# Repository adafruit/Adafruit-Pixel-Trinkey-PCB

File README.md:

## Adafruit Pixel Trinkey - USB Key for NeoPixel / DotStar Driving PCB

<a href="http://www.adafruit.com/products/5953"><br/>
Click here to purchase one from the Adafruit shop</a>

PCB files for the Adafruit Pixel Trinkey - USB Key for NeoPixel / DotStar Driving. 

Format is EagleCAD schematic and board layout
* https://www.adafruit.com/product/5953

### Description

Blast-off to Pixel Planet with the Adafruit Pixel Trinkey, a co-pilot for those who like to shine bright. This little microcontroller board plugs into your computer's USB port and can drive tons of NeoPixel (SK6812, WS2812, etc) or DotStar (e.g. AP102) LEDs without having to do any soldering or complex wiring. The SAMD21 chip on board has 32KB of SRAM, that means thousands of pixels! All from the convenience of your computer with support for Arduino, CircuitPython or Windows 11's built-in Dynamic Light Control

NeoPixels and Dotstars are 'smart' LEDs that can display 24-bit color, they're bright, colorful, individually-addressable, and come in dozens of different shapes: from flexible strips, to individual dots, to rings, and beyond. However, you need a microcontroller to drive them: something that can generate the exact pattern of data that they desire to set each pixel color. Normally folks use something like an Arduino, which will work just fine, but sometimes needs level shifting or separate power, or just has gangly wires.

This board contains the microcontroller, plus level shifting in a compact package that pokes out an inch from your computer USB port. On the end is a screw terminal block that can accept stranded or solid-core wires 26 to 18 AWG with four ports: 5V power, Data, Clock and Ground. If you're using DotStars, wire up the 'input' side of your LEDs to the 4 pads. If you're using NeoPixels, you can have one or two strands, where the second strand uses the Clock pin as the data generator.

Computer USB ports can provide up to 1A which we've found will drive about 150 pixels without difficulty as long as they are not all on full white at max brightness. If you need to drive a ton more pixels, simply disconnect the 5V power wire and use an external power source - just make sure that the ground wire from the external power is connected to the ground of the Trinkey+pixels. You can monitor the USB 5V line voltage thanks to a resistor divider on the board.

If you want to add additional circuitry, such as an Infrared remote input, or potentiometer, or a button, there's a JST-SH 3-pin connector on board. Use a JST SH 3-pin cable to access the 3V, ground and pin D4. There's also a separate mini NeoPixel for status feedback if desired.

Features:

* ATSAMD21E18 32-bit Cortex M0+ - 48 MHz 32-bit processor with 256KB Flash and 32 KB RAM
* Native USB supported by every OS - can be used in Arduino or CircuitPython as a USB serial console, MIDI, Keyboard/Mouse HID, and even a little disk drive for storing Python scripts
* Can be used with Arduino IDE or CircuitPython
* 0.1" / 2.54mm Terminal Blocks - Attach LEDs with no soldering! Just use a common screwdriver.
* On-board RGB NeoPixel LED
* JST SH 3-pin compatible connector - For extra hardware connectivity
* Reset switch to start your project code over or enter bootloader mode
* Open Source Hardware so you have full control over your LEDs

### License

Adafruit invests time and resources providing this open source design, please support Adafruit and open-source hardware by purchasing products from [Adafruit](https://www.adafruit.com)!

Designed by Limor Fried/Ladyada for Adafruit Industries.

Creative Commons Attribution/Share-Alike, all text above must be included in any redistribution. 
See license.txt for additional details.

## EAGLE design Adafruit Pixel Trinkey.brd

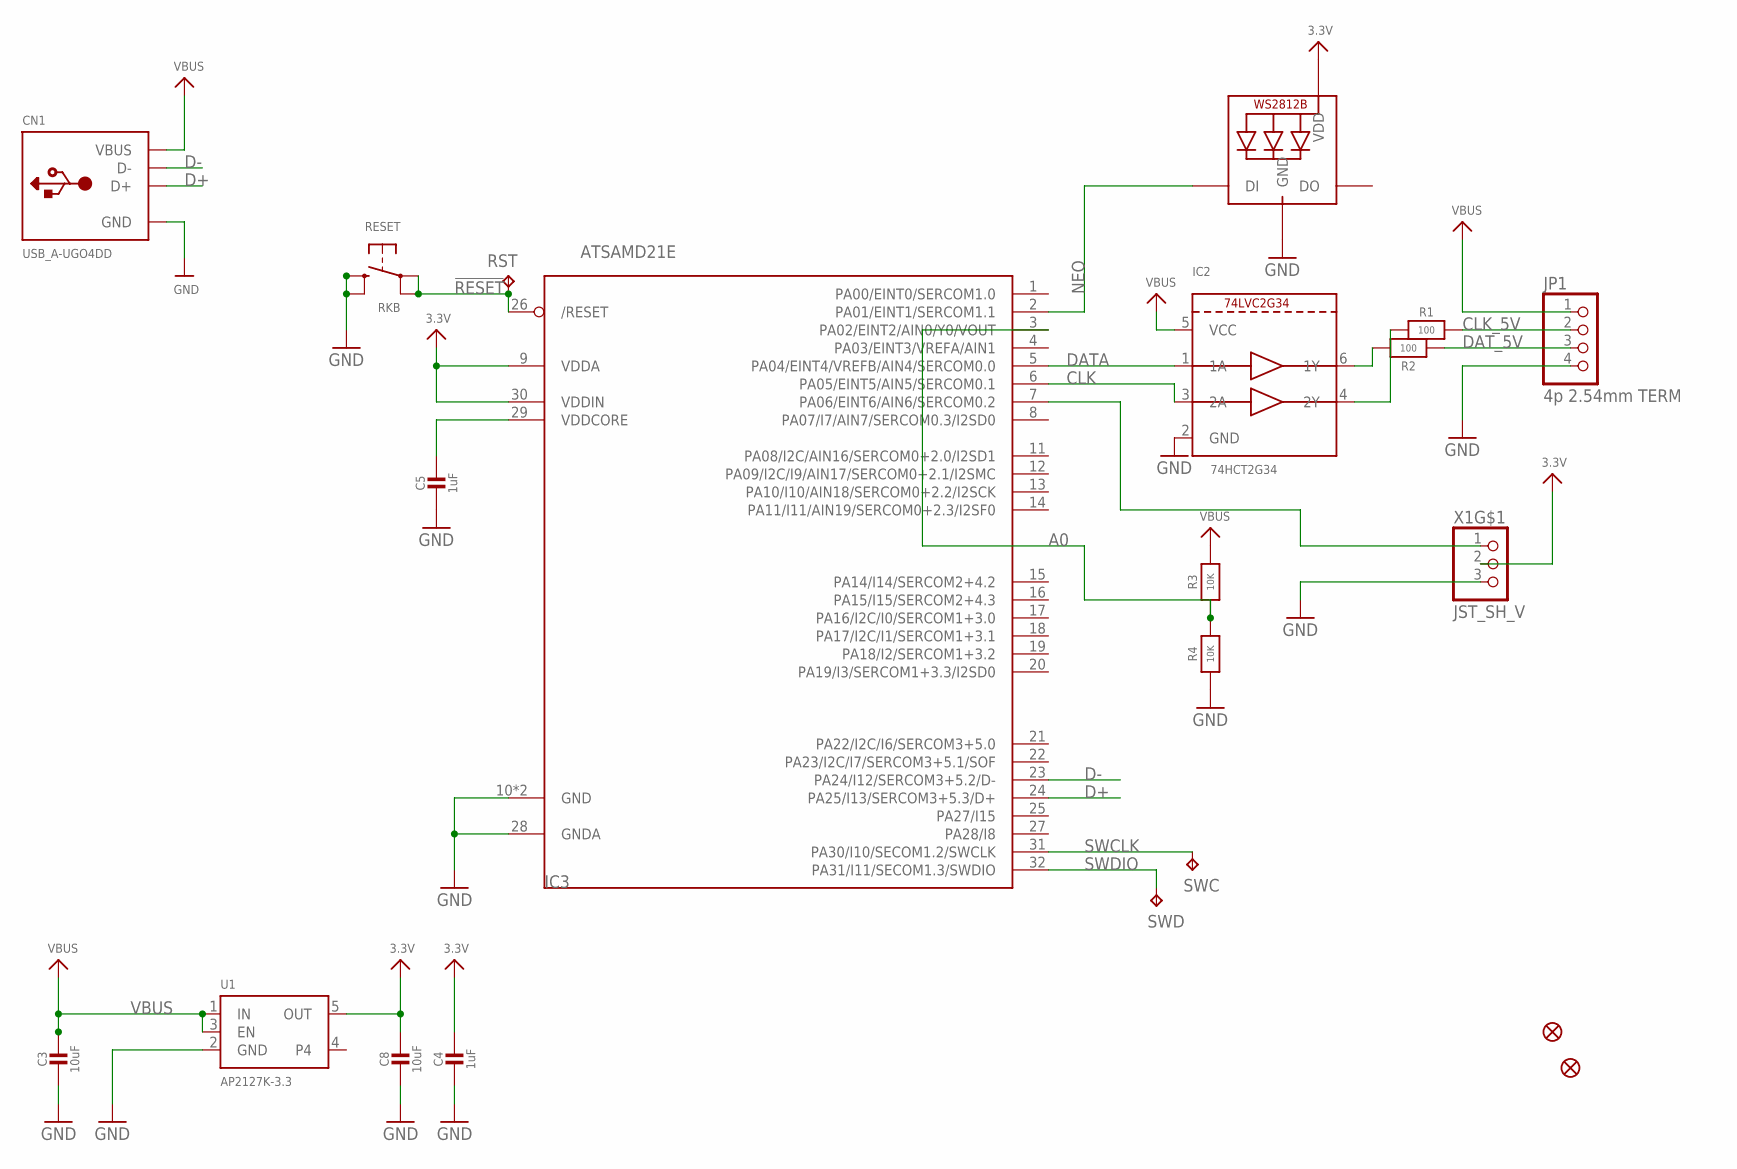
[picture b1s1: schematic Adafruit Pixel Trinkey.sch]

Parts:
C3, C8: 10uF; 0805-NO
C4, C5: 1uF; 0603-NO
CN1: USB_A-UGO4DD
FID1, FID2: FIDUCIAL_0.5MM
IC2: 74HCT2G34; SC70-6L
IC3: ATSAMD21E; QFN32_5MM
JP1: 4p 2.54mm TERM; 1X04_2.54MMTERMINAL
LED1: WS2812B_SK6805_1515; SK6805_1515
R1, R2: 100; _0402NO
R3, R4: 10K; _0402NO
RESET: RKB; BTN_RKB2_4.6X2.8
RST: TPTP16R; TP16R
SWC: TPTP15R; TP15R
SWD: TPTP16R; TP16R
U1: AP2127K-3.3; SOT23-5; JLC_ROTATION 0
X1: JST_SH_V; JST_SH3_RA

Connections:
3.3V: C4.1, C8.1, IC3.9 (VDDA), IC3.30 (VDDIN), LED1.2 (VDD), U1.5 (OUT), X1.2
!RESET: IC3.26 (/RESET), RESET.A, RESET.A' (P1), RST.TP
A0: IC3.3 (PA02/EINT2/AIN0/Y0/VOUT), R3.1, R4.2
CLK: IC2.3 (2A), IC3.6 (PA05/EINT5/AIN5/SERCOM0.1)
CLK_5V: JP1.2, R1.2
D+: CN1.D+, IC3.24 (PA25/I13/SERCOM3+5.3/D+)
D-: CN1.D-, IC3.23 (PA24/I12/SERCOM3+5.2/D-)
DATA: IC2.1 (1A), IC3.5 (PA04/EINT4/VREFB/AIN4/SERCOM0.0)
DAT_5V: JP1.3, R2.2
GND: C3.2, C4.2, C5.2, C8.2, CN1.GND, IC2.2 (GND), IC3.10 (GND), IC3.28 (GNDA), IC3.33 (GND), JP1.4, LED1.4 (GND), R4.1, RESET.B (S), RESET.B' (S1), U1.2 (GND), X1.3
unnamed: IC3.7 (PA06/EINT6/AIN6/SERCOM0.2), X1.1
unnamed: IC2.4 (2Y), R1.1
unnamed: IC2.6 (1Y), R2.1
NEO: IC3.2 (PA01/EINT1/SERCOM1.1), LED1.1 (DI)
SWCLK: IC3.31 (PA30/I10/SECOM1.2/SWCLK), SWC.TP
SWDIO: IC3.32 (PA31/I11/SECOM1.3/SWDIO), SWD.TP
VBUS: C3.1, CN1.VBUS, IC2.5 (VCC), JP1.1, R3.2, U1.1 (IN), U1.3 (EN)
VDDCORE1: C5.1, IC3.29 (VDDCORE)

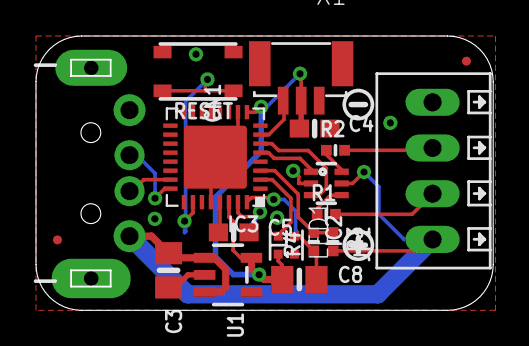
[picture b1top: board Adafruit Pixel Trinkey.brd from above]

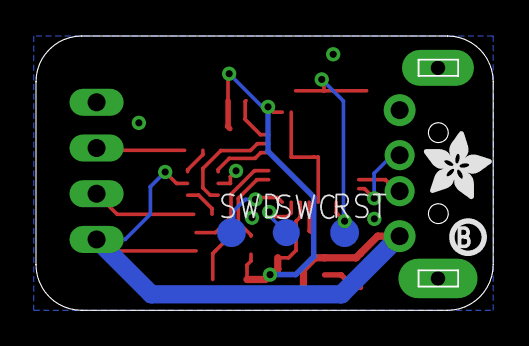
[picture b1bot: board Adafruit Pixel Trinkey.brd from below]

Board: 2 copper layers, 25.3 x 15.1 mm, 40 parts (15 on the bottom side), 18 nets.

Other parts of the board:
PLABEL0: PLABEL0
PLABEL1: PLABEL1
PLABEL2: PLABEL2
PLABEL3: PLABEL3
PLABEL4: PLABEL4
PLABEL5: PLABEL5
PLABEL6: PLABEL6
PLABEL7: PLABEL7
PLABEL8: PLABEL8
PLABEL9: PLABEL9
PLABEL10: PLABEL10
PLABEL11: PLABEL11
PLABEL12: PLABEL12
PLABEL13: PLABEL13
PLABEL14: PLABEL14
U$8: PCBFEAT-REV-040
U$9: SYMBOL_PLUS
U$10: SYMBOL_MINUS
U$12: ADAFRUIT_3.5MM

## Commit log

2024-05-23 cookiecutter
2024-05-23 prettypins

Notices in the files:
parts and their libraries:
microbuilder: This work is placed in the public domain, and may be freely used for commercial and non-commercial work with the following conditions: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
